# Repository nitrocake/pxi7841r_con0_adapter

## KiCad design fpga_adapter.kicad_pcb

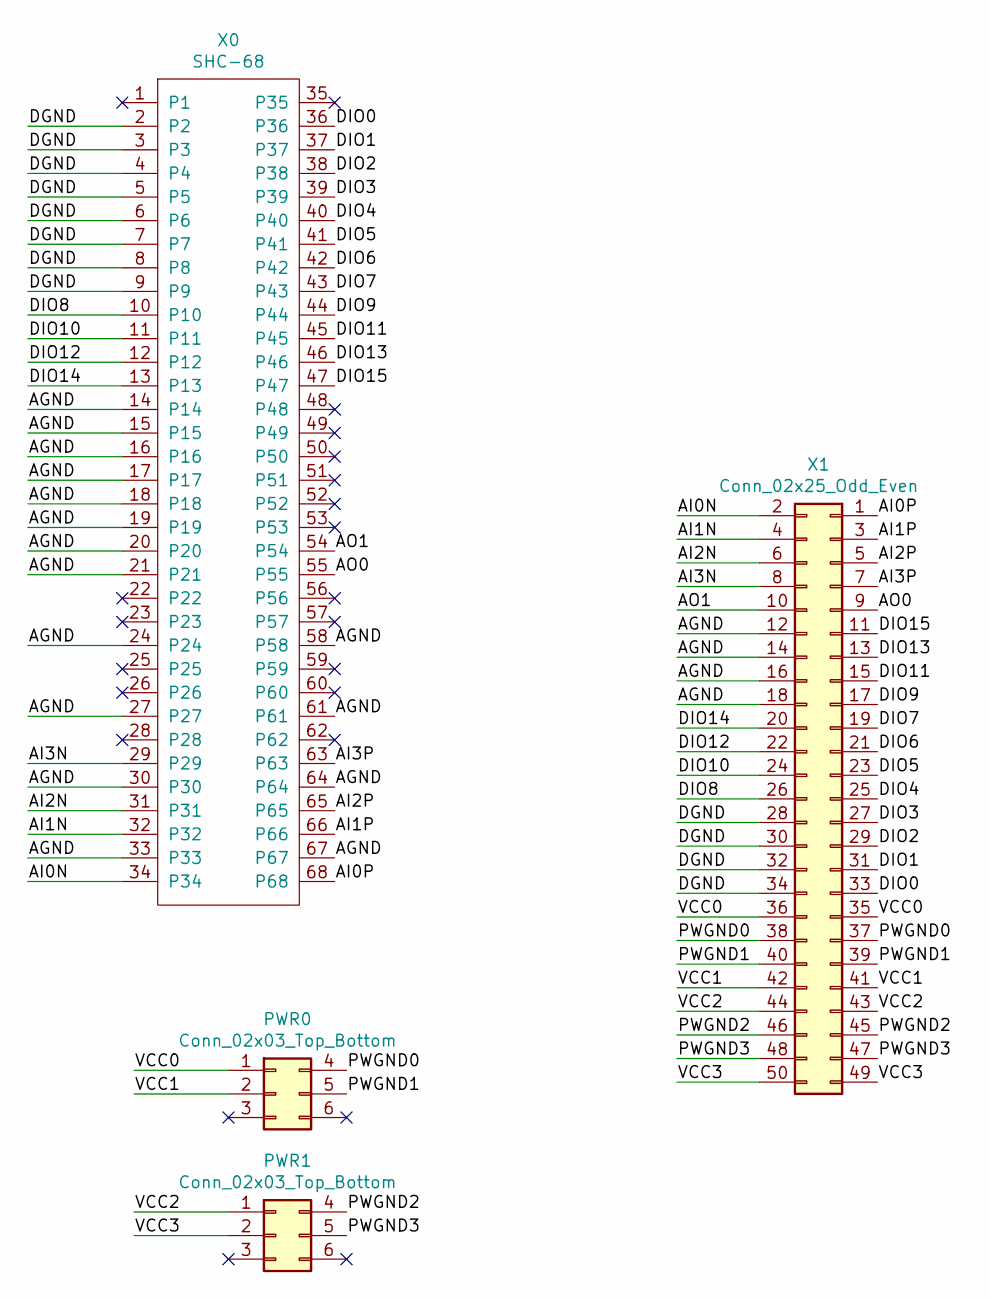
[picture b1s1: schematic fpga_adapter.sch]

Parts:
PWR0, PWR1: Conn_02x03_Top_Bottom; Molex_Mini-Fit_Jr_5569-06A2_2x03_P4.20mm_Horizontal
X0: SHC-68; SHC-68_PAD
X1: Conn_02x25_Odd_Even; IDC-Header_2x25-1MP_P2.54mm_Latch_Vertical

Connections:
/AGND: X0.14, X0.15, X0.16, X0.17, X0.18, X0.19, X0.20, X0.21, X0.24, X0.27, X0.30, X0.33, X0.58, X0.61, X0.64, X0.67, X1.12, X1.14, X1.16, X1.18
/AI0N: X0.34, X1.2
/AI0P: X0.68, X1.1
/AI1N: X0.32, X1.4
/AI1P: X0.66, X1.3
/AI2N: X0.31, X1.6
/AI2P: X0.65, X1.5
/AI3N: X0.29, X1.8
/AI3P: X0.63, X1.7
/AO0: X0.55, X1.9
/AO1: X0.54, X1.10
/DGND: X0.2, X0.3, X0.4, X0.5, X0.6, X0.7, X0.8, X0.9, X1.28, X1.30, X1.32, X1.34
/DIO0: X0.36, X1.33
/DIO1: X0.37, X1.31
/DIO2: X0.38, X1.29
/DIO3: X0.39, X1.27
/DIO4: X0.40, X1.25
/DIO5: X0.41, X1.23
/DIO6: X0.42, X1.21
/DIO7: X0.43, X1.19
/DIO8: X0.10, X1.26
/DIO9: X0.44, X1.17
/DIO10: X0.11, X1.24
/DIO11: X0.45, X1.15
/DIO12: X0.12, X1.22
/DIO13: X0.46, X1.13
/DIO14: X0.13, X1.20
/DIO15: X0.47, X1.11
/PWGND0: PWR0.4, X1.37, X1.38
/PWGND1: PWR0.5, X1.39, X1.40
/PWGND2: PWR1.4, X1.45, X1.46
/PWGND3: PWR1.5, X1.47, X1.48
/VCC0: PWR0.1, X1.35, X1.36
/VCC1: PWR0.2, X1.41, X1.42
/VCC2: PWR1.1, X1.43, X1.44
/VCC3: PWR1.2, X1.49, X1.50

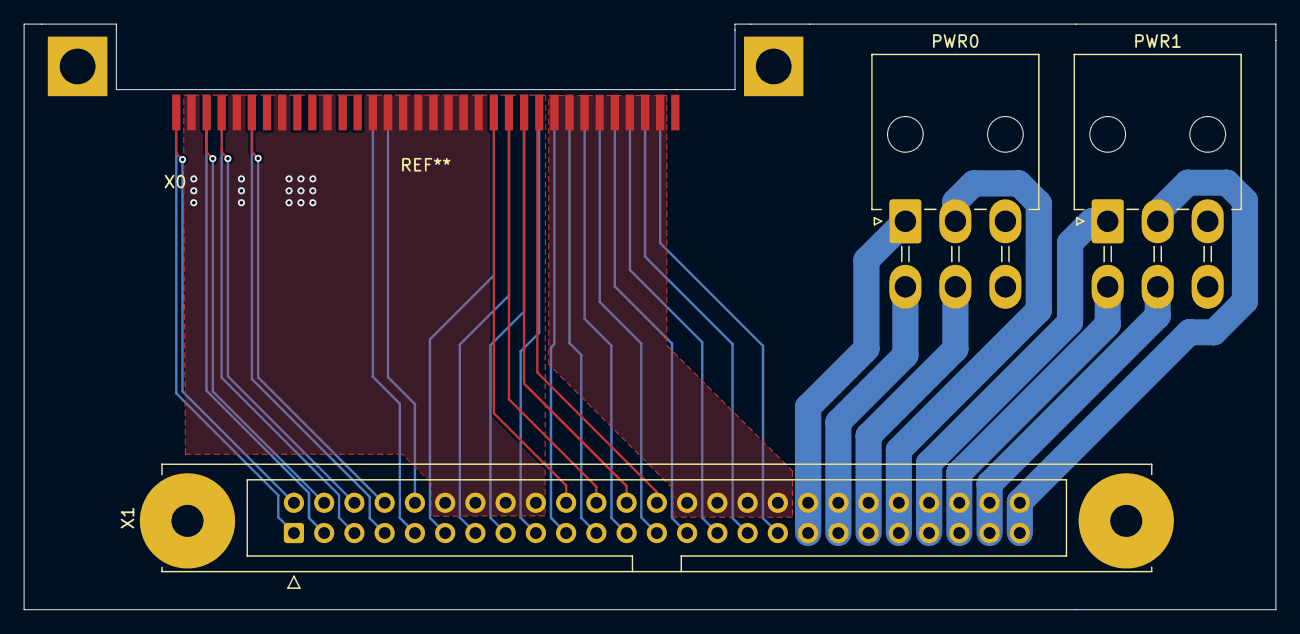
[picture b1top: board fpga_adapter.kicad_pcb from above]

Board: 2 copper layers, 105.1 x 49.2 mm, 4 parts (0 on the bottom side), 36 nets.

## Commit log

2021-10-20 finished routing
2021-10-24 completed board routing
